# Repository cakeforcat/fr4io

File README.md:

# FR4io
This is an attempt at creating a modular set of tiles that can create movement systems from factorio in real life.
## Proposed features
 - smart, addressable tiles
 - fully reconfigurable
 - hot-swappable
 - extendable (arms, splitters, combiners)
 - magnetically actuated
 - low-cost-ish

## magnetic actuation
each tile will consist of 5 PCB coils that can be thought of as a very crude linear motor. Payload to be moved are purely for aesthetics and will be as light as possible.
The tile will be able to sense the presense of a payload by measuring the current on each coil through a shunt resistor.

## network
tiles connect to each other through a simple UART link. Each powered on tile announces it's presence on all 4 edges abd nearby tiles respond with acknowledges. The entire graph is built and maintained by the central controller. The firmware on each tile is meant to be as minimal as possible to allow for OTW (Over the Wire) updates. All higher level functions are to be implemented on the controller. Each tile is addressable.

## EMF
will hopefully be presented at EMF2026? will depend on tickets and if we actually make it :D

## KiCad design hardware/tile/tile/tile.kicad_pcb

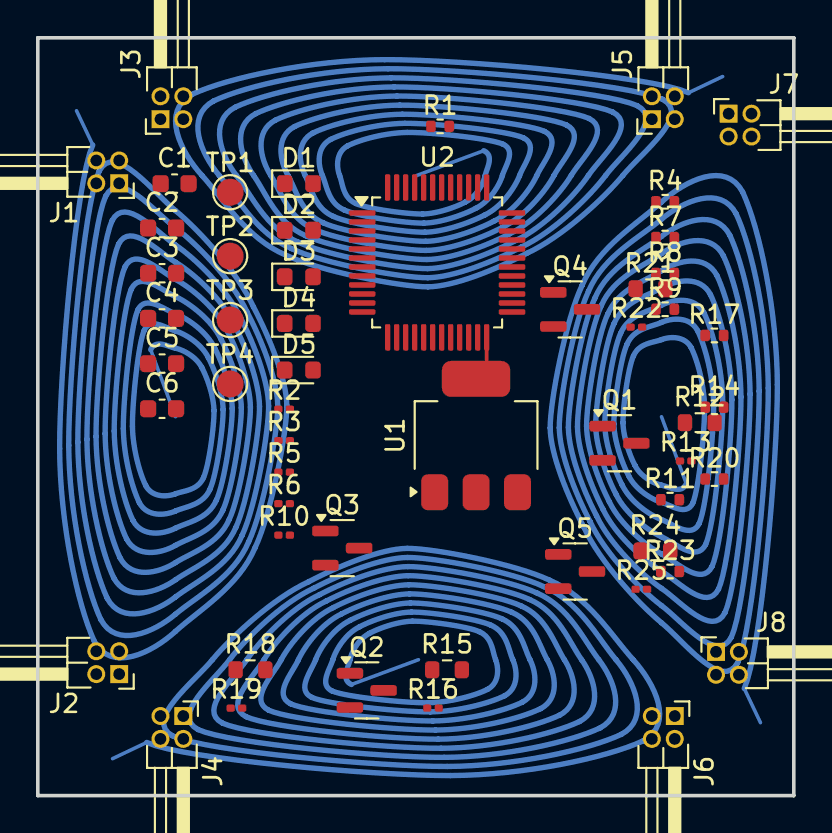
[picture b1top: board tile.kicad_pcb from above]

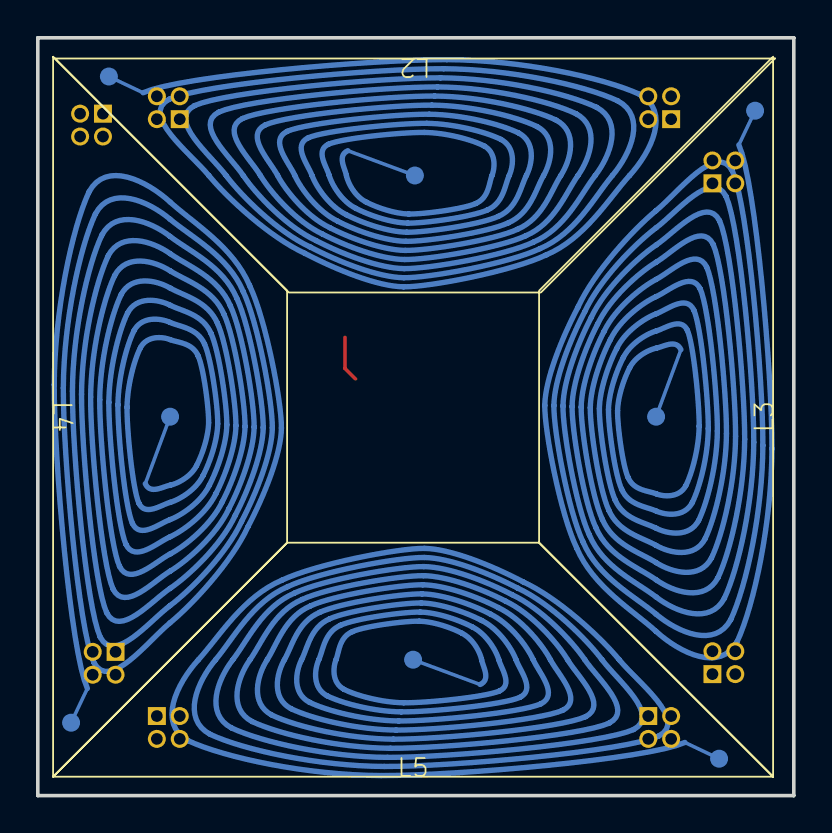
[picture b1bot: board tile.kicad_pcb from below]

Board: 4 copper layers, 42.0 x 42.1 mm, 59 parts (4 on the bottom side), 46 nets.

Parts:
C1, C3: 10uF; C_0603_1608Metric
C2, C4: 100nF; C_0603_1608Metric
C5, C6: 0.1uF; C_0603_1608Metric
D1, D2, D3, D4, D5: LED; LED_0603_1608Metric
J1, J2, J3, J4, J5, J6, J7, J8: Conn_02x02_Counter_Clockwise; PinHeader_2x02_P1.27mm_Horizontal
L2, L3, L4, L5: L; coil_done
Q1, Q2, Q3, Q4, Q5: AO3400A; SOT-23
R1, R4, R9: 10K; R_0402_1005Metric
R2, R3, R5, R6, R10: 330R; R_0201_0603Metric
R7: 220K; R_0402_1005Metric
R8: 100K; R_0402_1005Metric
R11, R14, R17, R20, R23: 10R; R_0402_1005Metric
R12, R15, R18, R21, R24: 10K; R_0603_1608Metric
R13, R16, R19, R22, R25: 1R; R_0201_0603Metric
TP1, TP2, TP3, TP4: PROG; TestPoint_Pad_D1.5mm
U1: AMS1117-3.3; SOT-223-3_TabPin2
U2: CH32V203C8T6; LQFP-48_7x7mm_P0.5mm

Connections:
+3V3: C3.1, C4.1, C5.1, C6.1, R2.1, R4.2, R9.2, TP3.1, U1.2 (VO), U2.1 (VBAT), U2.9 (VDDA), U2.24 (VDD_VIO), U2.36 (VDD), U2.48 (VDD)
+9V: C1.1, C2.1, J1.1, J2.2, J3.4, J4.1, J5.3, J6.2, J7.4, J8.3, L2.1, L3.1, L4.1, L5.1, R7.2, U1.3 (VI)
/ADC_IN0: R13.1, U2.10 (PA0)
/ADC_IN1: L2.2, R16.1, U2.11 (PA1)
/ADC_IN4: L3.2, R19.1, U2.14 (PA4)
/ADC_IN5: L4.2, R22.1, U2.15 (PA5)
/ADC_IN6: L5.2, R25.1, U2.16 (PA6)
/ADC_IN7: R7.1, R8.2, U2.17 (PA7)
/BOOT0: R4.1, U2.44 (BOOT0)
/BOOT1: R1.2, U2.20 (PB2)
/COIL1: R11.1, U2.39 (PB3)
/COIL2: R14.1, U2.40 (PB4)
/COIL3: R17.1, U2.41 (PB5)
/COIL4: R20.1, U2.42 (PB6)
/COIL5: R23.1, U2.43 (PB7)
/LED1: R3.1, U2.25 (PB12)
/LED2: R5.1, U2.26 (PB13)
/LED3: R6.1, U2.27 (PB14)
/LED4: R10.1, U2.28 (PB15)
/NRST: R9.1, U2.7 (~RST)
/SWCLK: TP2.1, U2.37 (SWCLK)
/SWDIO: TP1.1, U2.34 (SWDIO)
/USART1_RX: J2.3, J2.4, U2.31 (PA10)
/USART1_TX: J1.3, J1.4, U2.30 (PA9)
/USART2_RX: J7.1, J7.2, U2.13 (PA3)
/USART2_TX: J8.1, J8.2, U2.12 (PA2)
/USART3_RX: J6.3, J6.4, U2.22 (PB11)
/USART3_TX: J4.3, J4.4, U2.21 (PB10)
/USART4_RX: J3.1, J3.2, U2.19 (PB1)
/USART4_TX: J5.1, J5.2, U2.18 (PB0)
GND: C1.2, C2.2, C3.2, C4.2, C5.2, C6.2, D1.1 (K), D2.1 (K), D3.1 (K), D4.1 (K), D5.1 (K), J1.2, J2.1, J3.3, J4.2, J5.4, J6.1, J7.3, J8.4, Q1.2 (S), Q2.2 (S), Q3.2 (S), Q4.2 (S), Q5.2 (S), R1.1, R8.1, R12.2, R15.2, R18.2, R21.2, R24.2, TP4.1, U1.1 (GND), U2.8 (VSSA), U2.23 (VSS), U2.35 (VSS), U2.47 (VSS)
unnamed: D1.2 (A), R2.2
unnamed: D2.2 (A), R3.2
unnamed: D3.2 (A), R5.2
unnamed: D4.2 (A), R6.2
unnamed: D5.2 (A), R10.2
unnamed: Q1.3 (D), R13.2
unnamed: Q1.1 (G), R11.2, R12.1
unnamed: Q2.3 (D), R16.2
unnamed: Q2.1 (G), R14.2, R15.1
unnamed: Q3.3 (D), R19.2
unnamed: Q3.1 (G), R17.2, R18.1
unnamed: Q4.3 (D), R22.2
unnamed: Q4.1 (G), R20.2, R21.1
unnamed: Q5.3 (D), R25.2
unnamed: Q5.1 (G), R23.2, R24.1

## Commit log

2025-12-30 add LICENSE
    Added the CERN Open Hardware Licence Version 2 - Strongly Reciprocal to the project.
2025-12-30 add README
2025-12-30 add tile kicad project
2025-12-31 init schematic for tile
2026-01-03 tile schematic v1
2026-01-04 add debug, make tile schematic pretty
2026-01-04 add vin sense to tile
2026-01-04 fix tile sense resistors
2026-03-09 added coils will improve them later
